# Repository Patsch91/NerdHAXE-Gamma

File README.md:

**The NerdHaxe-Gamma is a 6-Asic-Miner based on the [NerdQAxe+(+)](https://github.com/shufps/qaxe) / [Nerdaxe](https://github.com/BitMaker-hub/NerdAxeUltra) and inspired by [OSMU](https://osmu.wiki/) and the [Bitaxe](https://github.com/bitaxeorg)**

Current status: First version is running pretty solid. Disclaimer: This is a hobby project and not a professional or commercial product so feel free to build / make changes and share ideas on how to improve the design

# Specifications
- **Open Source:** All design files are provided, and suggestions/improvements are always welcome.
- **Standalone:** Using the T-Display S3 with WiFi and works without an external controller.
- **Performance:** ~7.35 TH/s average at around 120-125 watts (measured at the wall, including a MW UHP-200-12).
- **Case:** DIY Idea for a 3D-printed case with an integrated PSU.

# Software / Firmware
The NerdHaxe-Gamma uses the [ESP-Miner](https://github.com/shufps/ESP-Miner-NerdQAxePlus) by shufps and the [Webflasher](https://shufps.github.io/nerdqaxe-web-flasher/) is recommended as the easiest way to flash the NerdHaxe-Gamma (or any other Nerd*axe variant). It uses the official releases and is always up to date.
<br> The screen displays key values and parameters, such as the current hashrate, session runtime, fan speed, and more.
<br><br> 
<br> Via your browser, you can monitor all important aspects, such as the hashrate graph, adjust settings like core voltage and fan speed, define a fallback stratum pool, or simply check the logs.
<br><br> 

# Components
- **Asics:** 6 x BM1370
- **T-Display S3:** ESP32S3 microcontroller with WiFi and integrated display
- **PCB:** I ordered the prototype PCB as specified in the KiCad files above, with a copper thickness of 1/1 oz, and it has been running well so far. One thing I tried on this PCB was exposing the pads underneath the ASICs to improve thermal connection to the backside of the PCB, where 10x10mm heatsinks can be placed.
- **BOM:** The board components needed for the build can be found in the BOM.
- **Heatsink:** The PCB has slotted holes that accommodate mounting patterns from 75x75mm to 80x80mm. The mounting patterns fit some LGA15xx or 2011 coolers, but be mindful of the thermal contact area of the coolers you want to use. Most standard coolers have a contact area of around 40x40mm, which is not sufficient. Therefore, I used server heatsinks such as the Supermicro SNK-P0048P(W) with a completely flat contact surface.
- **Fans:** Currently, I am using 2x Noctua A9x25 PWM chromax fans in a push-pull configuration, and at 75-85% PWM, the sound level is quite ok. I will soon test the Arctic P9 Max model, which is more powerful than the Noctuas, but of course, at a higher noise level.
- **PSU:** The NerdHaxe-Gamma operates at around 12V and 10A with default settings. Therefore, I recommend using a PSU that provides 12V and at least 15A. I am using the Meanwell UHP-200-12. <br>

# Misc 
**DISCLAIMER:** This device is an *advanced* build and partly WIP. To get 6 Asics soldered properly *can* be very hard and frustrating if you are not used to soldering Asics or soldering in general. Using that amount of power, this device is not a toy, and you should know what you are doing. Follow the regulations and precautions – **stay safe!** <br>

If you like this project and want to support future work, feel free to donate to: **`bc1q0ctaxeha3lpsaaz7kpjulflw2d9p66fhkp48dk`**

or related projects without which this project would not have been possible for me:

[NerdQAxe+](https://github.com/shufps/qaxe)

[OSMU](https://osmu.wiki/)

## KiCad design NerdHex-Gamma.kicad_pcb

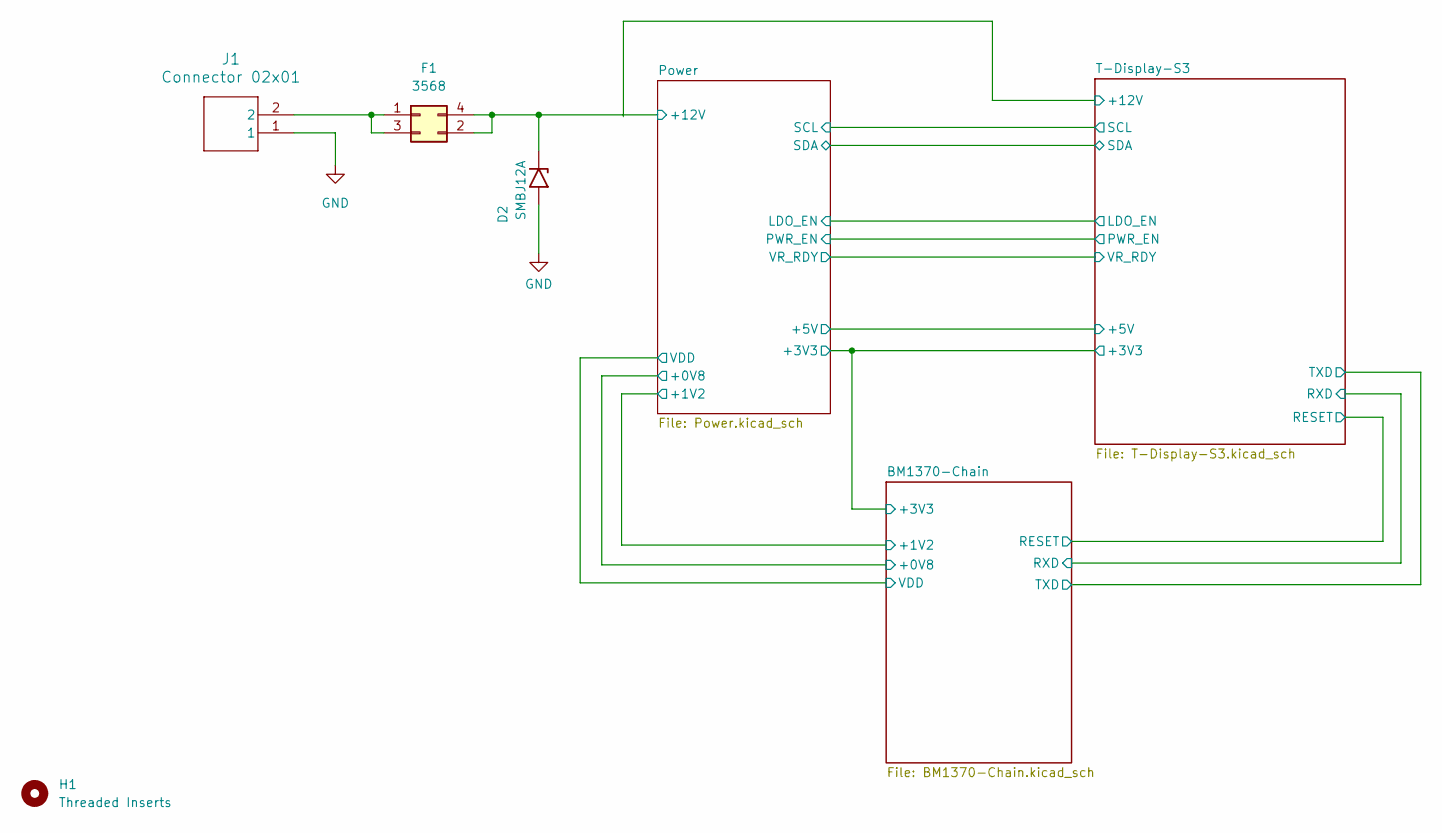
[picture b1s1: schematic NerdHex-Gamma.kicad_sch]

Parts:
D2: SMBJ12A; D_SMB
F1: 3568; Fuseholder Blade_3568; PARTREV C
H1: Threaded Inserts
J1: Connector 02x01; CONN2

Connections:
+12V: D2.1 (A1), F1.2, F1.4; also elsewhere on the board
GND: D2.2 (A2), J1.1; also elsewhere on the board
unnamed: F1.1, F1.3, J1.2

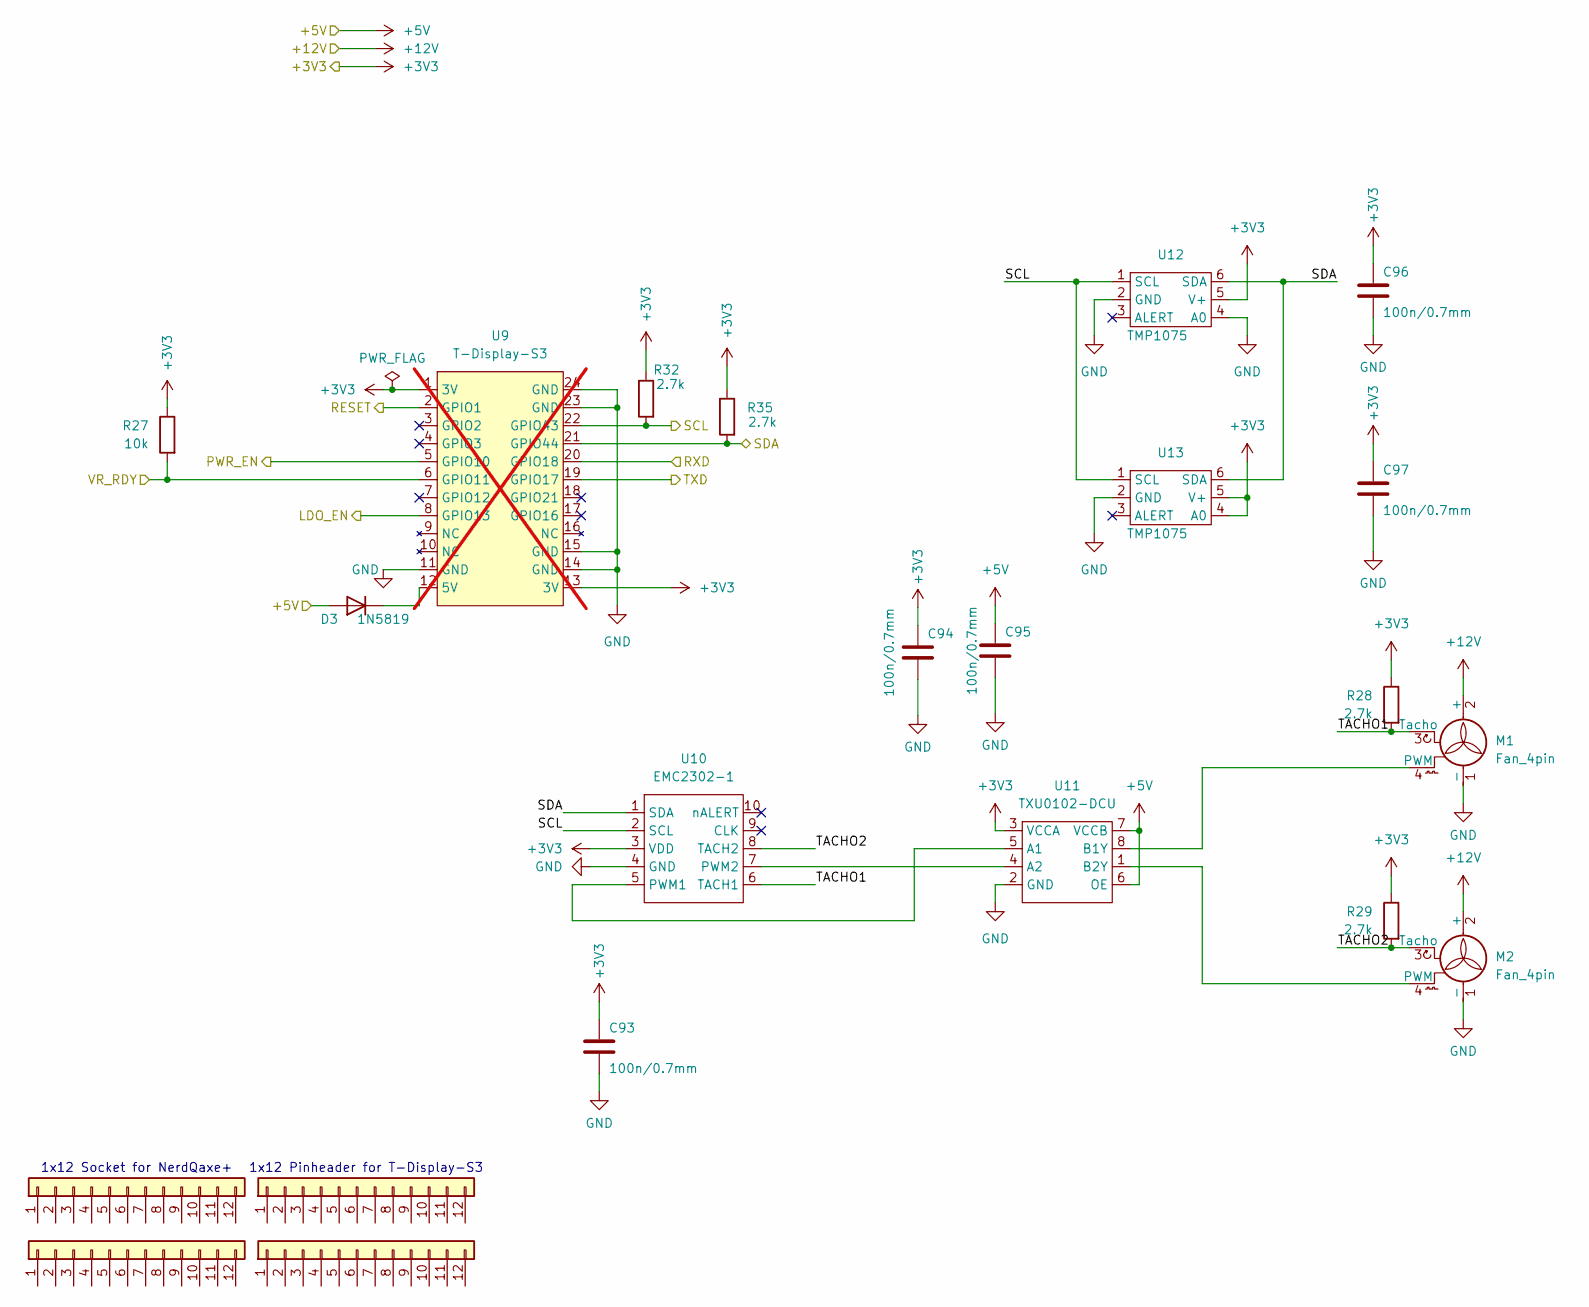
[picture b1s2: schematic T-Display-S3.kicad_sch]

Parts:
C93, C94, C95, C96, C97: 100n/0.7mm; C_0805_2012Metric
D3: 1N5819; D_SOD-123
J4, J5: Conn_01x12-Socket
J6, J7: Conn_01x12-Header
M1, M2: Fan_4pin; FanPinHeader_1x04_P2.54mm_Vertical
R27: 10k; R_0805_2012Metric
R28, R29, R32, R35: 2.7k; R_0805_2012Metric
U9: T-Display-S3; not fitted
U10: EMC2302-1; MSOP-10_3x3mm_P0.5mm
U11: TXU0102-DCU; VSSOP-8_2.3x2mm_P0.5mm
U12, U13: TMP1075; TMP1075-DRL

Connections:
+3V3: C93.1, C94.1, C96.1, C97.1, R27.1, R28.1, R29.1, R32.1, R35.1, U9.1 (3V), U9.13 (3V), U10.3 (VDD), U11.3 (VCCA), U12.5 (V+), U13.4 (A0), U13.5 (V+); also elsewhere on the board
+5V: C95.1, D3.2 (A), U11.6 (OE), U11.7 (VCCB); also elsewhere on the board
+12V: M1.2 (+), M2.2 (+); also elsewhere on the board
/BM1370-Chain/RESET: U9.2 (GPIO1); also elsewhere on the board
/BM1370-Chain/RXD: U9.20 (GPIO18); also elsewhere on the board
/BM1370-Chain/TXD: U9.19 (GPIO17); also elsewhere on the board
/Power/LDO_EN: U9.8 (GPIO13); also elsewhere on the board
/Power/PWR_EN: U9.5 (GPIO10); also elsewhere on the board
/Power/VR_RDY: R27.2, U9.6 (GPIO11); also elsewhere on the board
/T-Display-S3/SCL: R32.2, U9.22 (GPIO43), U10.2 (SCL), U12.1 (SCL), U13.1 (SCL); also elsewhere on the board
/T-Display-S3/SDA: R35.2, U9.21 (GPIO44), U10.1 (SDA), U12.6 (SDA), U13.6 (SDA); also elsewhere on the board
/T-Display-S3/TACHO1: M1.3 (Tacho), R28.2, U10.6 (TACH1)
/T-Display-S3/TACHO2: M2.3 (Tacho), R29.2, U10.8 (TACH2)
GND: C93.2, C94.2, C95.2, C96.2, C97.2, M1.1 (-), M2.1 (-), U9.11 (GND), U9.14 (GND), U9.15 (GND), U9.23 (GND), U9.24 (GND), U10.4 (GND), U11.2 (GND), U12.2 (GND), U12.4 (A0), U13.2 (GND); also elsewhere on the board
unnamed: D3.1 (K), U9.12 (5V)
unnamed: M1.4 (PWM), U11.8 (B1Y)
unnamed: M2.4 (PWM), U11.1 (B2Y)
unnamed: U10.5 (PWM1), U11.5 (A1)
unnamed: U10.7 (PWM2), U11.4 (A2)

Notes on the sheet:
1x12 Socket for NerdQaxe+
1x12 Pinheader for T-Display-S3

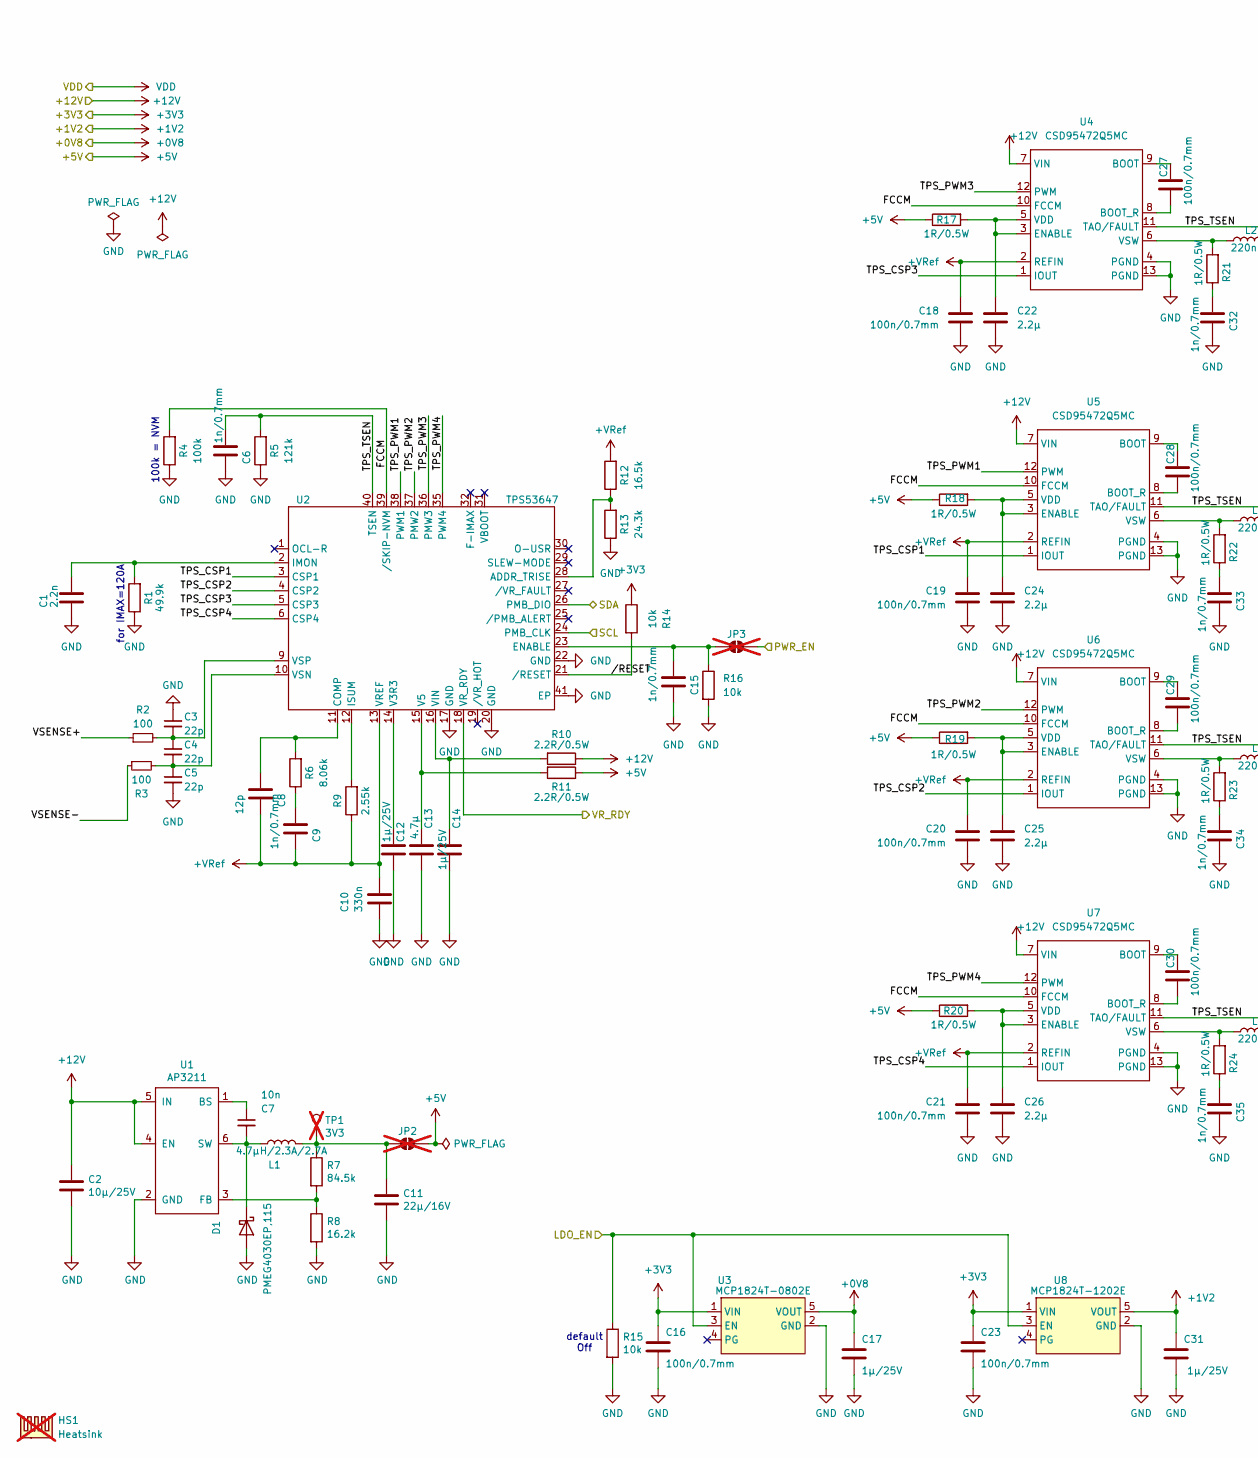
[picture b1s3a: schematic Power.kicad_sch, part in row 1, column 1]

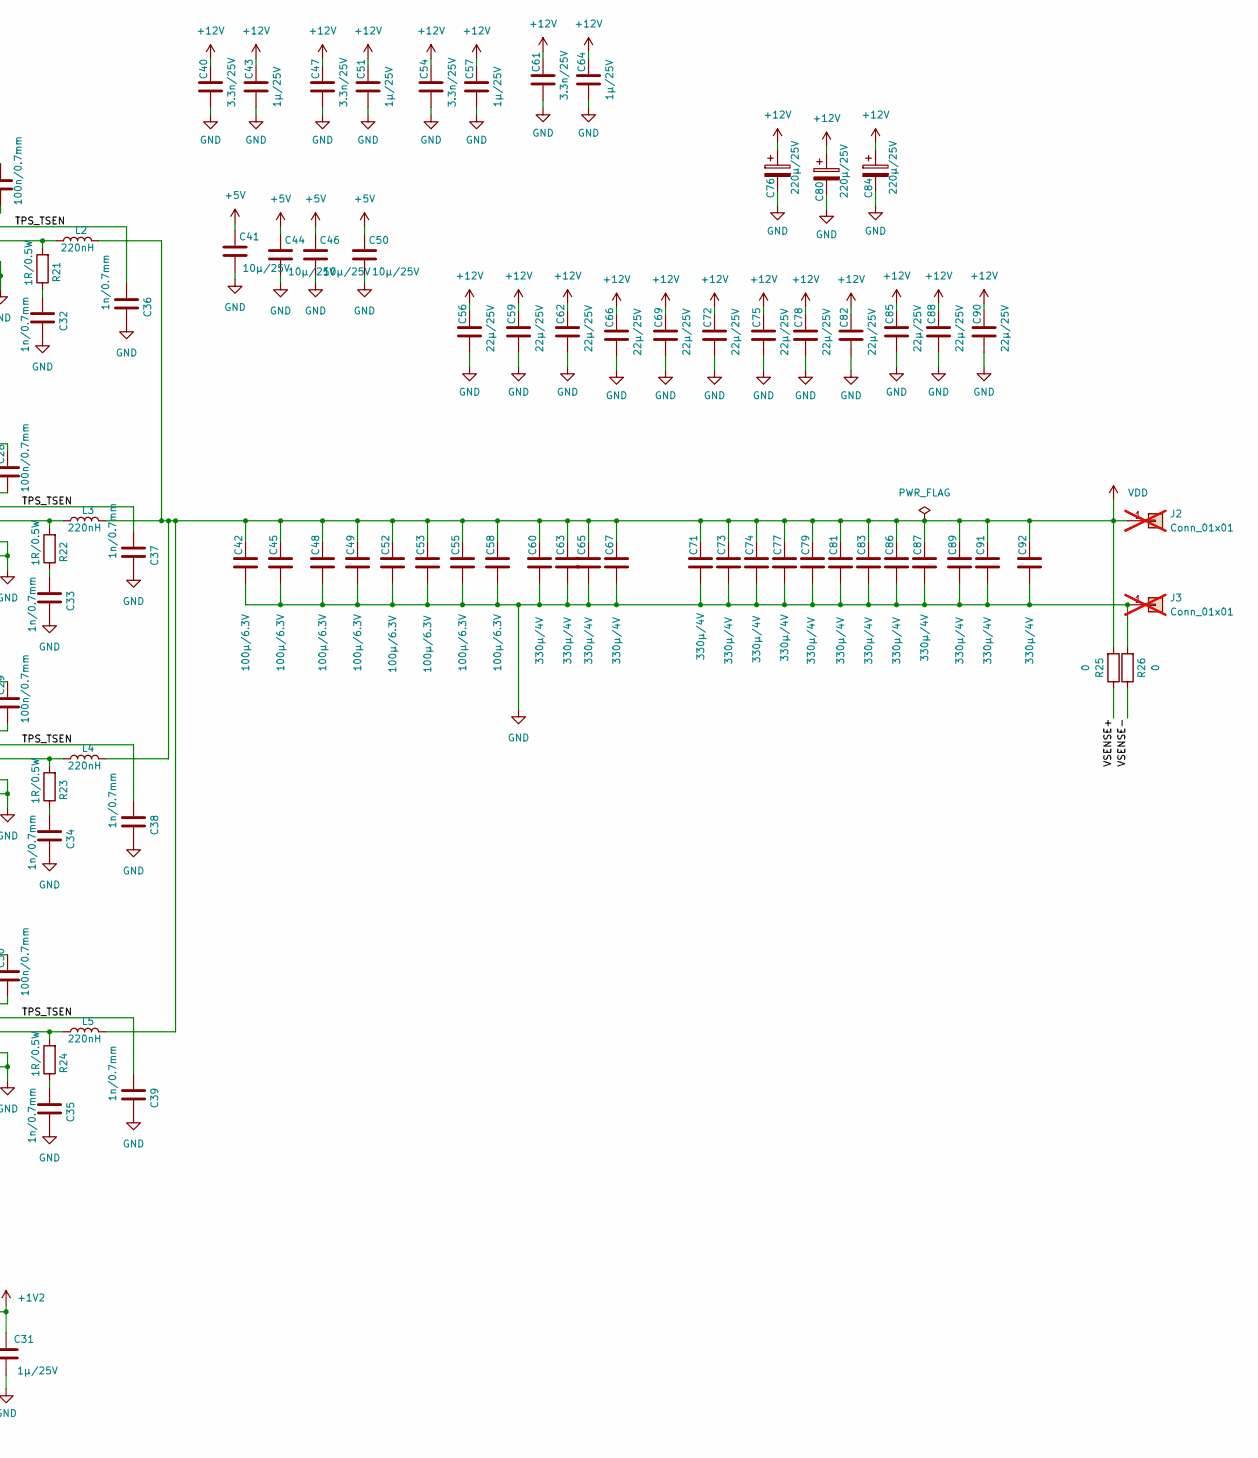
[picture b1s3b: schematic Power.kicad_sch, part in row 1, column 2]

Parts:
C1: 2.2n; C_0805_2012Metric
C2, C41, C44, C46, C50: 10µ/25V; C_0805_2012Metric
C3, C4, C5: 22p; C_0603_1608Metric
C6, C9, C15, C32, C33, C34, C35, C36, C37, C38, C39: 1n/0.7mm; C_0805_2012Metric
C7: 10n; C_0805_2012Metric
C8: 12p; C_0603_1608Metric
C10: 330n; C_0805_2012Metric
C11: 22µ/16V; C_1206_3216Metric
C12, C14, C17, C31, C43, C51, C57, C64: 1µ/25V; C_0805_2012Metric
C13: 4.7µ; C_0805_2012Metric
C16, C18, C19, C20, C21, C23, C27, C28, C29, C30: 100n/0.7mm; C_0805_2012Metric
C22, C24, C25, C26: 2.2µ; C_0805_2012Metric
C40, C47, C54, C61: 3.3n/25V; C_0805_2012Metric
C42, C45, C48, C49, C52, C53, C55, C58: 100µ/6.3V; C_1210_3225Metric
C56, C59, C62, C66, C69, C72, C75, C78, C82, C85, C88, C90: 22µ/25V; C_1210_3225Metric
C60, C63, C65, C67, C71, C73, C74, C77, C79, C81, C83, C86, C87, C89, C91, C92: 330µ/4V; C_1210_3225Metric
C76, C80, C84: 220µ/25V; CP_Elec_8x10
D1: PMEG4030EP,115; D_SOD-128
HS1: Heatsink; not fitted
J2, J3: Conn_01x01; Wuerth_REDCUBE-THR_WP-THRBU_74650194_THR; not fitted
JP2, JP3: SolderJumper_2_Open; SolderJumper-2_P1.3mm_Open_RoundedPad1.0x1.5mm; not fitted
L1: 4.7µH/2.3A/2.7A; L_Taiyo-Yuden_NR-50xx
L2, L3, L4, L5: 220nH; IFLR-4031GC-01-8x10
R1: 49.9k; R_0805_2012Metric
R2, R3: 100; R_0805_2012Metric
R4: 100k; R_0805_2012Metric
R5: 121k; R_0805_2012Metric
R6: 8.06k; R_0805_2012Metric
R7: 84.5k; R_0805_2012Metric
R8: 16.2k; R_0805_2012Metric
R9: 2.55k; R_0805_2012Metric
R10, R11: 2.2R/0.5W; R_0805_2012Metric
R12: 16.5k; R_0805_2012Metric
R13: 24.3k; R_0805_2012Metric
R14, R15, R16: 10k; R_0805_2012Metric
R17, R18, R19, R20, R21, R22, R23, R24: 1R/0.5W; R_0805_2012Metric
R25, R26: 0; R_0805_2012Metric
TP1: 3V3; TestPoint_Pad_2.0x2.0mm; not fitted
U1: AP3211; SOT-23-6
U2: TPS53647; Texas_RHA0040B_VQFN-40-1EP_6x6mm_P0.5mm_EP4.15x4.15mm_Therm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
U3: MCP1824T-0802E; SOT-23-5
U4, U5, U6, U7: CSD95472Q5MC; CSD95472-SON-5x6
U8: MCP1824T-1202E; SOT-23-5

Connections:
+0V8: C17.1, U3.5 (VOUT); also elsewhere on the board
+1V2: C31.1, U8.5 (VOUT); also elsewhere on the board
+3V3: C16.1, C23.1, R14.1, U3.1 (VIN), U8.1 (VIN); also elsewhere on the board
+5V: C41.1, C44.1, C46.1, C50.1, JP2.2 (B), R11.1, R17.1, R18.1, R19.1, R20.1; also elsewhere on the board
+12V: C2.1, C40.1, C43.1, C47.1, C51.1, C54.1, C56.1, C57.1, C59.1, C61.1, C62.1, C64.1, C66.1, C69.1, C72.1, C75.1, C76.1, C78.1, C80.1, C82.1, C84.1, C85.1, C88.1, C90.1, R10.1, U1.4 (EN), U1.5 (IN), U4.7 (VIN), U5.7 (VIN), U6.7 (VIN), U7.7 (VIN); also elsewhere on the board
+VRef: C8.2, C9.2, C10.1, C18.1, C19.1, C20.1, C21.1, R9.1, R12.2, U2.13 (VREF), U4.2 (REFIN), U5.2 (REFIN), U6.2 (REFIN), U7.2 (REFIN)
/Power/FCCM: R4.2, U2.39 (/SKIP-NVM), U4.10 (FCCM), U5.10 (FCCM), U6.10 (FCCM), U7.10 (FCCM)
/Power/LDO_EN: R15.1, U3.3 (EN), U8.3 (EN); also elsewhere on the board
/Power/PWR_EN: JP3.2 (B); also elsewhere on the board
/Power/TPS_CSP1: U2.3 (CSP1), U5.1 (IOUT)
/Power/TPS_CSP2: U2.4 (CSP2), U6.1 (IOUT)
/Power/TPS_CSP3: U2.5 (CSP3), U4.1 (IOUT)
/Power/TPS_CSP4: U2.6 (CSP4), U7.1 (IOUT)
/Power/TPS_PWM1: U2.38 (PWM1), U5.12 (PWM)
/Power/TPS_PWM2: U2.37 (PMW2), U6.12 (PWM)
/Power/TPS_PWM3: U2.36 (PMW3), U4.12 (PWM)
/Power/TPS_PWM4: U2.35 (PWM4), U7.12 (PWM)
/Power/TPS_TSEN: C6.1, C36.1, C37.1, C38.1, C39.1, R5.2, U2.40 (TSEN), U4.11 (TAO/FAULT), U5.11 (TAO/FAULT), U6.11 (TAO/FAULT), U7.11 (TAO/FAULT)
/Power/VR_RDY: U2.18 (VR_RDY); also elsewhere on the board
/Power/VSENSE+: R2.1, R25.1
/Power/VSENSE-: R3.1, R26.1
/Power//RESET: R14.2, U2.21 (/RESET)
/T-Display-S3/SCL: U2.24 (PMB_CLK); also elsewhere on the board
/T-Display-S3/SDA: U2.26 (PMB_DIO); also elsewhere on the board
GND: C1.2, C2.2, C3.1, C5.2, C6.2, C10.2, C11.2, C12.2, C13.1, C14.1, C15.2, C16.2, C17.2, C18.2, C19.2, C20.2, C21.2, C22.2, C23.2, C24.2, C25.2, C26.2, C31.2, C32.2, C33.2, C34.2, C35.2, C36.2, C37.2, C38.2, C39.2, C40.2, C41.2, C42.2, C43.2, C44.2, C45.2, C46.2, C47.2, C48.2, C49.2, C50.2, C51.2, C52.2, C53.2, C54.2, C55.2, C56.2, C57.2, C58.2, C59.2, C60.2, C61.2, C62.2, C63.2, C64.2, C65.2, C66.2, C67.2, C69.2, C71.2, C72.2, C73.2, C74.2, C75.2, C76.2, C77.2, C78.2, C79.2, C80.2, C81.2, C82.2, C83.2, C84.2, C85.2, C86.2, C87.2, C88.2, C89.2, C90.2, C91.2, C92.2, D1.2 (A), J3.1, R1.1, R4.1, R5.1, R8.2, R13.1, R15.2, R16.2, R26.2, U1.2 (GND), U2.17 (GND), U2.20 (GND), U2.22 (GND), U2.41 (EP), U3.2 (GND), U4.4 (PGND), U4.13 (PGND), U5.4 (PGND), U5.13 (PGND), U6.4 (PGND), U6.13 (PGND), U7.4 (PGND), U7.13 (PGND), U8.2 (GND); also elsewhere on the board
unnamed: C9.1, R6.1
unnamed: C32.1, R21.1
unnamed: C33.1, R22.1
unnamed: C34.1, R23.1
unnamed: C35.1, R24.1
unnamed: C7.2, D1.1 (K), L1.1, U1.6 (SW)
unnamed: C11.1, JP2.1 (A), L1.2, R7.1, TP1.1
unnamed: C15.1, JP3.1 (A), R16.1, U2.23 (ENABLE)
unnamed: C7.1, U1.1 (BS)
unnamed: R7.2, R8.1, U1.3 (FB)
unnamed: R12.1, R13.2, U2.28 (ADDR_TRISE)
unnamed: C8.1, R6.2, U2.11 (COMP)
unnamed: C1.1, R1.2, U2.2 (IMON)
unnamed: R9.2, U2.12 (ISUM)
unnamed: C12.1, U2.14 (V3R3)
unnamed: C13.2, R11.2, U2.15 (V5)
unnamed: C14.2, R10.2, U2.16 (VIN)
unnamed: C4.2, C5.1, R3.2, U2.10 (VSN)
unnamed: C3.2, C4.1, R2.2, U2.9 (VSP)
unnamed: C27.1, U4.9 (BOOT)
unnamed: C27.2, U4.8 (BOOT_R)
unnamed: C22.1, R17.2, U4.3 (ENABLE), U4.5 (VDD)
unnamed: L2.1, R21.2, U4.6 (VSW)
unnamed: C28.1, U5.9 (BOOT)
unnamed: C28.2, U5.8 (BOOT_R)
unnamed: C24.1, R18.2, U5.3 (ENABLE), U5.5 (VDD)
unnamed: L3.1, R22.2, U5.6 (VSW)
unnamed: C29.1, U6.9 (BOOT)
unnamed: C29.2, U6.8 (BOOT_R)
unnamed: C25.1, R19.2, U6.3 (ENABLE), U6.5 (VDD)
unnamed: L4.1, R23.2, U6.6 (VSW)
unnamed: C30.1, U7.9 (BOOT)
unnamed: C30.2, U7.8 (BOOT_R)
unnamed: C26.1, R20.2, U7.3 (ENABLE), U7.5 (VDD)
unnamed: L5.1, R24.2, U7.6 (VSW)
VDD: C42.1, C45.1, C48.1, C49.1, C52.1, C53.1, C55.1, C58.1, C60.1, C63.1, C65.1, C67.1, C71.1, C73.1, C74.1, C77.1, C79.1, C81.1, C83.1, C86.1, C87.1, C89.1, C91.1, C92.1, J2.1, L2.2, L3.2, L4.2, L5.2, R25.2; also elsewhere on the board

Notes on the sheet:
100k = NVM
default Off
for IMAX=120A

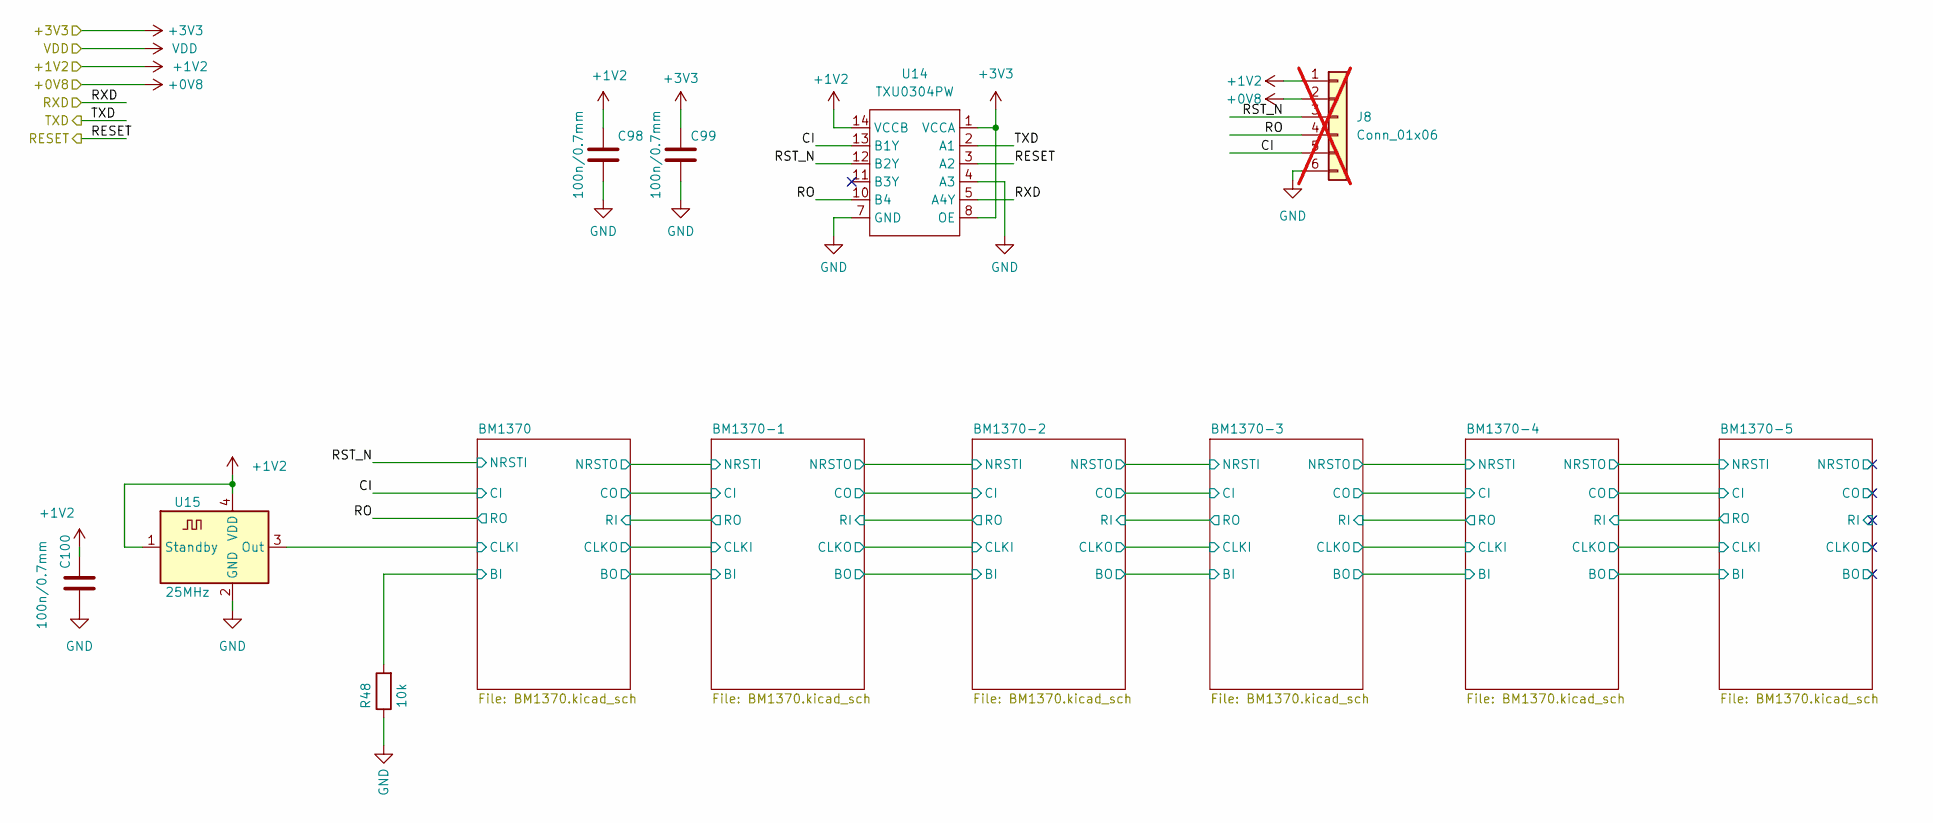
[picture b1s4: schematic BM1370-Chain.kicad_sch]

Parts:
C98, C99, C100: 100n/0.7mm; C_0805_2012Metric
J8: Conn_01x06; PinHeader_1x06_P1.27mm_Vertical; not fitted
R48: 10k; R_0805_2012Metric
U14: TXU0304PW; TSSOP-14-1EP_4.4x5mm_P0.65mm
U15: 25MHz; Oscillator_SMD_EuroQuartz_XO32-4Pin_3.2x2.5mm

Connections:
+0V8: J8.2; also elsewhere on the board
+1V2: C98.1, C100.1, J8.1, U14.14 (VCCB), U15.1 (Standby), U15.4 (VDD); also elsewhere on the board
+3V3: C99.1, U14.1 (VCCA), U14.8 (OE); also elsewhere on the board
/BM1370-Chain/BM1370/BI: R48.2; also elsewhere on the board
/BM1370-Chain/BM1370/CLKI: U15.3 (Out); also elsewhere on the board
/BM1370-Chain/CI: J8.5, U14.13 (B1Y); also elsewhere on the board
/BM1370-Chain/RESET: U14.3 (A2); also elsewhere on the board
/BM1370-Chain/RO: J8.4, U14.10 (B4); also elsewhere on the board
/BM1370-Chain/RST_N: J8.3, U14.12 (B2Y); also elsewhere on the board
/BM1370-Chain/RXD: U14.5 (A4Y); also elsewhere on the board
/BM1370-Chain/TXD: U14.2 (A1); also elsewhere on the board
GND: C98.2, C99.2, C100.2, J8.6, R48.1, U14.4 (A3), U14.7 (GND), U15.2 (GND); also elsewhere on the board

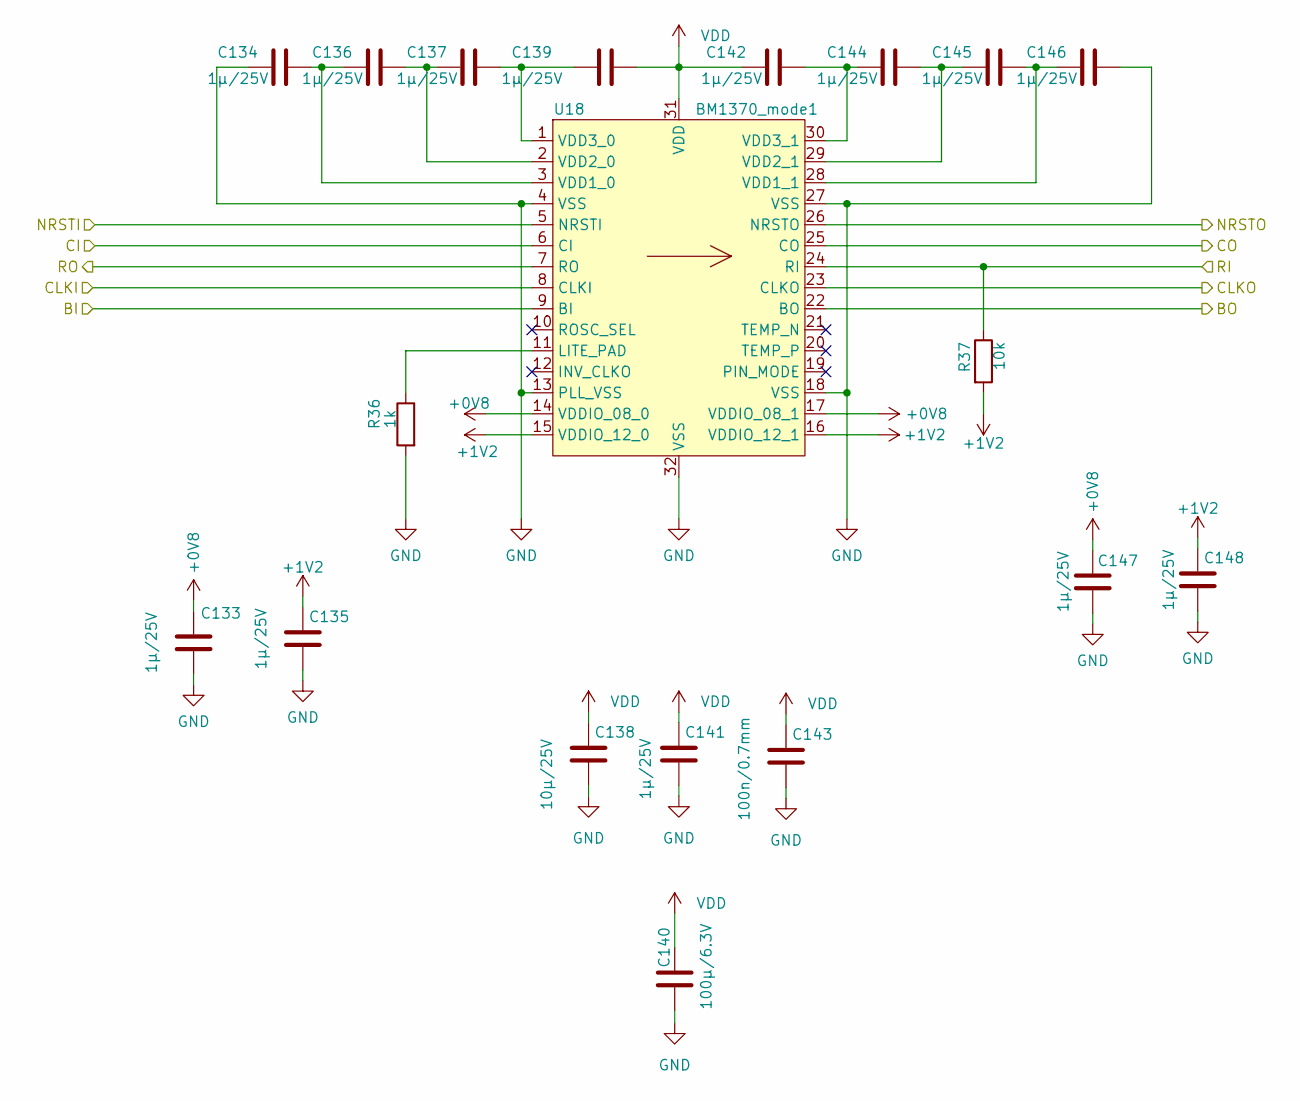
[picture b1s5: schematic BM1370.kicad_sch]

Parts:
C133, C134, C135, C136, C137, C139, C141, C142, C144, C145, C146, C147, C148: 1µ/25V; C_0805_2012Metric
C138: 10µ/25V; C_0805_2012Metric
C140: 100µ/6.3V; C_1210_3225Metric
C143: 100n/0.7mm; C_0805_2012Metric
R36: 1k; R_0805_2012Metric
R37: 10k; R_0805_2012Metric
U18: BM1370_mode1; BM1370

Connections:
+0V8: C133.2, C147.2, U18.14 (VDDIO_08_0), U18.17 (VDDIO_08_1); also elsewhere on the board
+1V2: C135.1, C148.1, R37.2, U18.15 (VDDIO_12_0), U18.16 (VDDIO_12_1); also elsewhere on the board
/BM1370-Chain/BM1370-1/BO: U18.9 (BI); also elsewhere on the board
/BM1370-Chain/BM1370-1/CLKO: U18.8 (CLKI); also elsewhere on the board
/BM1370-Chain/BM1370-1/CO: U18.6 (CI); also elsewhere on the board
/BM1370-Chain/BM1370-1/NRSTO: U18.5 (NRSTI); also elsewhere on the board
/BM1370-Chain/BM1370-1/RI: U18.7 (RO); also elsewhere on the board
/BM1370-Chain/BM1370-2/BO: U18.22 (BO); also elsewhere on the board
/BM1370-Chain/BM1370-2/CLKO: U18.23 (CLKO); also elsewhere on the board
/BM1370-Chain/BM1370-2/CO: U18.25 (CO); also elsewhere on the board
/BM1370-Chain/BM1370-2/NRSTO: U18.26 (NRSTO); also elsewhere on the board
/BM1370-Chain/BM1370-2/RI: R37.1, U18.24 (RI); also elsewhere on the board
GND: C133.1, C134.1, C135.2, C138.2, C140.2, C141.2, C143.2, C146.2, C147.1, C148.2, R36.2, U18.4 (VSS), U18.13 (PLL_VSS), U18.18 (VSS), U18.27 (VSS), U18.32 (VSS); also elsewhere on the board
unnamed: R36.1, U18.11 (LITE_PAD)
unnamed: C134.2, C136.1, U18.3 (VDD1_0)
unnamed: C145.2, C146.1, U18.28 (VDD1_1)
unnamed: C136.2, C137.1, U18.2 (VDD2_0)
unnamed: C144.2, C145.1, U18.29 (VDD2_1)
unnamed: C137.2, C139.1, U18.1 (VDD3_0)
unnamed: C142.2, C144.1, U18.30 (VDD3_1)
VDD: C138.1, C139.2, C140.1, C141.1, C142.1, C143.1, U18.31 (VDD); also elsewhere on the board

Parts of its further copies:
C101, C102, C103, C104, C105, C106, C107, C108, C109, C110, C111, C112, C114, C117, C118, C119, C120, C121, C123, C125, C126, C128, C129, C130, C131, C132, C149, C150, C151, C152, C153, C155, C157, C158, C160, C161, C162, C163, C164, C165, C166, C167, C168, C169, C171, C173, C174, C176, C177, C178, C179, C180, C181, C182, C183, C184, C185, C187, C189, C190, C192, C193, C194, C195, C196: 1µ/25V; C_0805_2012Metric
C113, C122, C154, C170, C186: 10µ/25V; C_0805_2012Metric
C115, C127, C159, C175, C191: 100n/0.7mm; C_0805_2012Metric
C116, C124, C156, C172, C188: 100µ/6.3V; C_1210_3225Metric
R30, R33, R39, R42, R45: 1k; R_0805_2012Metric
R31, R34, R40, R43, R46: 10k; R_0805_2012Metric
U16, U17, U19, U20, U21: BM1370_mode1; BM1370

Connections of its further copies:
+0V8: C109.2, C110.2, C117.2, C131.2, C149.2, C163.2, C165.2, C179.2, C181.2, C195.2, U16.14 (VDDIO_08_0), U16.17 (VDDIO_08_1), U17.14 (VDDIO_08_0), U17.17 (VDDIO_08_1), U19.14 (VDDIO_08_0), U19.17 (VDDIO_08_1), U20.14 (VDDIO_08_0), U20.17 (VDDIO_08_1), U21.14 (VDDIO_08_0), U21.17 (VDDIO_08_1); also elsewhere on the board
+1V2: C111.1, C112.1, C119.1, C132.1, C151.1, C164.1, C167.1, C180.1, C183.1, C196.1, R31.2, R34.2, R40.2, R43.2, R46.2, U16.15 (VDDIO_12_0), U16.16 (VDDIO_12_1), U17.15 (VDDIO_12_0), U17.16 (VDDIO_12_1), U19.15 (VDDIO_12_0), U19.16 (VDDIO_12_1), U20.15 (VDDIO_12_0), U20.16 (VDDIO_12_1), U21.15 (VDDIO_12_0), U21.16 (VDDIO_12_1); also elsewhere on the board
/BM1370-Chain/BM1370-1/BI: U16.22 (BO), U17.9 (BI)
/BM1370-Chain/BM1370-1/BO: U17.22 (BO); also elsewhere on the board
/BM1370-Chain/BM1370-1/CI: U16.25 (CO), U17.6 (CI)
/BM1370-Chain/BM1370-1/CLKI: U16.23 (CLKO), U17.8 (CLKI)
/BM1370-Chain/BM1370-1/CLKO: U17.23 (CLKO); also elsewhere on the board
/BM1370-Chain/BM1370-1/CO: U17.25 (CO); also elsewhere on the board
/BM1370-Chain/BM1370-1/NRSTI: U16.26 (NRSTO), U17.5 (NRSTI)
/BM1370-Chain/BM1370-1/NRSTO: U17.26 (NRSTO); also elsewhere on the board
/BM1370-Chain/BM1370-1/RI: R34.1, U17.24 (RI); also elsewhere on the board
/BM1370-Chain/BM1370-1/RO: R31.1, U16.24 (RI), U17.7 (RO)
/BM1370-Chain/BM1370-2/BO: U19.9 (BI); also elsewhere on the board
/BM1370-Chain/BM1370-2/CLKO: U19.8 (CLKI); also elsewhere on the board
/BM1370-Chain/BM1370-2/CO: U19.6 (CI); also elsewhere on the board
/BM1370-Chain/BM1370-2/NRSTO: U19.5 (NRSTI); also elsewhere on the board
/BM1370-Chain/BM1370-2/RI: U19.7 (RO); also elsewhere on the board
/BM1370-Chain/BM1370-3/BO: U19.22 (BO), U20.9 (BI)
/BM1370-Chain/BM1370-3/CLKO: U19.23 (CLKO), U20.8 (CLKI)
/BM1370-Chain/BM1370-3/CO: U19.25 (CO), U20.6 (CI)
/BM1370-Chain/BM1370-3/NRSTO: U19.26 (NRSTO), U20.5 (NRSTI)
/BM1370-Chain/BM1370-3/RI: R40.1, U19.24 (RI), U20.7 (RO)
/BM1370-Chain/BM1370-4/BO: U20.22 (BO), U21.9 (BI)
/BM1370-Chain/BM1370-4/CLKO: U20.23 (CLKO), U21.8 (CLKI)
/BM1370-Chain/BM1370-4/CO: U20.25 (CO), U21.6 (CI)
/BM1370-Chain/BM1370-4/NRSTO: U20.26 (NRSTO), U21.5 (NRSTI)
/BM1370-Chain/BM1370-4/RI: R43.1, U20.24 (RI), U21.7 (RO)
/BM1370-Chain/BM1370-5/BO: U21.22 (BO)
/BM1370-Chain/BM1370-5/CLKO: U21.23 (CLKO)
/BM1370-Chain/BM1370-5/CO: U21.25 (CO)
/BM1370-Chain/BM1370-5/NRSTO: U21.26 (NRSTO)
/BM1370-Chain/BM1370-5/RI: R46.1, U21.24 (RI)
/BM1370-Chain/BM1370/BI: U16.9 (BI); also elsewhere on the board
/BM1370-Chain/BM1370/CLKI: U16.8 (CLKI); also elsewhere on the board
/BM1370-Chain/CI: U16.6 (CI); also elsewhere on the board
/BM1370-Chain/RO: U16.7 (RO); also elsewhere on the board
/BM1370-Chain/RST_N: U16.5 (NRSTI); also elsewhere on the board
GND: C101.1, C108.2, C109.1, C110.1, C111.2, C112.2, C113.2, C114.2, C115.2, C116.2, C117.1, C118.1, C119.2, C122.2, C124.2, C125.2, C127.2, C130.2, C131.1, C132.2, C149.1, C150.1, C151.2, C154.2, C156.2, C157.2, C159.2, C162.2, C163.1, C164.2, C165.1, C166.1, C167.2, C170.2, C172.2, C173.2, C175.2, C178.2, C179.1, C180.2, C181.1, C182.1, C183.2, C186.2, C188.2, C189.2, C191.2, C194.2, C195.1, C196.2, R30.2, R33.2, R39.2, R42.2, R45.2, U16.4 (VSS), U16.13 (PLL_VSS), U16.18 (VSS), U16.27 (VSS), U16.32 (VSS), U17.4 (VSS), U17.13 (PLL_VSS), U17.18 (VSS), U17.27 (VSS), U17.32 (VSS), U19.4 (VSS), U19.13 (PLL_VSS), U19.18 (VSS), U19.27 (VSS), U19.32 (VSS), U20.4 (VSS), U20.13 (PLL_VSS), U20.18 (VSS), U20.27 (VSS), U20.32 (VSS), U21.4 (VSS), U21.13 (PLL_VSS), U21.18 (VSS), U21.27 (VSS), U21.32 (VSS); also elsewhere on the board
unnamed: R30.1, U16.11 (LITE_PAD)
unnamed: C101.2, C102.1, U16.3 (VDD1_0)
unnamed: C107.2, C108.1, U16.28 (VDD1_1)
unnamed: C102.2, C103.1, U16.2 (VDD2_0)
unnamed: C106.2, C107.1, U16.29 (VDD2_1)
unnamed: C103.2, C104.1, U16.1 (VDD3_0)
unnamed: C105.2, C106.1, U16.30 (VDD3_1)
unnamed: R33.1, U17.11 (LITE_PAD)
unnamed: C118.2, C120.1, U17.3 (VDD1_0)
unnamed: C129.2, C130.1, U17.28 (VDD1_1)
unnamed: C120.2, C121.1, U17.2 (VDD2_0)
unnamed: C128.2, C129.1, U17.29 (VDD2_1)
unnamed: C121.2, C123.1, U17.1 (VDD3_0)
unnamed: C126.2, C128.1, U17.30 (VDD3_1)
unnamed: R39.1, U19.11 (LITE_PAD)
unnamed: C150.2, C152.1, U19.3 (VDD1_0)
unnamed: C161.2, C162.1, U19.28 (VDD1_1)
unnamed: C152.2, C153.1, U19.2 (VDD2_0)
unnamed: C160.2, C161.1, U19.29 (VDD2_1)
unnamed: C153.2, C155.1, U19.1 (VDD3_0)
unnamed: C158.2, C160.1, U19.30 (VDD3_1)
unnamed: R42.1, U20.11 (LITE_PAD)
unnamed: C166.2, C168.1, U20.3 (VDD1_0)
unnamed: C177.2, C178.1, U20.28 (VDD1_1)
unnamed: C168.2, C169.1, U20.2 (VDD2_0)
unnamed: C176.2, C177.1, U20.29 (VDD2_1)
unnamed: C169.2, C171.1, U20.1 (VDD3_0)
unnamed: C174.2, C176.1, U20.30 (VDD3_1)
unnamed: R45.1, U21.11 (LITE_PAD)
unnamed: C182.2, C184.1, U21.3 (VDD1_0)
unnamed: C193.2, C194.1, U21.28 (VDD1_1)
unnamed: C184.2, C185.1, U21.2 (VDD2_0)
unnamed: C192.2, C193.1, U21.29 (VDD2_1)
unnamed: C185.2, C187.1, U21.1 (VDD3_0)
unnamed: C190.2, C192.1, U21.30 (VDD3_1)
VDD: C104.2, C105.1, C113.1, C114.1, C115.1, C116.1, C122.1, C123.2, C124.1, C125.1, C126.1, C127.1, C154.1, C155.2, C156.1, C157.1, C158.1, C159.1, C170.1, C171.2, C172.1, C173.1, C174.1, C175.1, C186.1, C187.2, C188.1, C189.1, C190.1, C191.1, U16.31 (VDD), U17.31 (VDD), U19.31 (VDD), U20.31 (VDD), U21.31 (VDD); also elsewhere on the board
